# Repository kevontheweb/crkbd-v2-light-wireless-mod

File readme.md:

# corne v2 light wireless mod

- [x] change to use more generic kicad 8/9 symbols/footprints
- [x] use the DRC
- [x] add jst for battery
- [ ] pwr switch
- [ ] remove reset switch?
- [x] add the pins on the pro micro footprint for battery
- [x] aesthetic changes (font, hatched copper pour)
- [x] ~panelise~ mouse bites
- [x] use smd diodes
- [x] remove choc support (would rather have a proper choc spacing)

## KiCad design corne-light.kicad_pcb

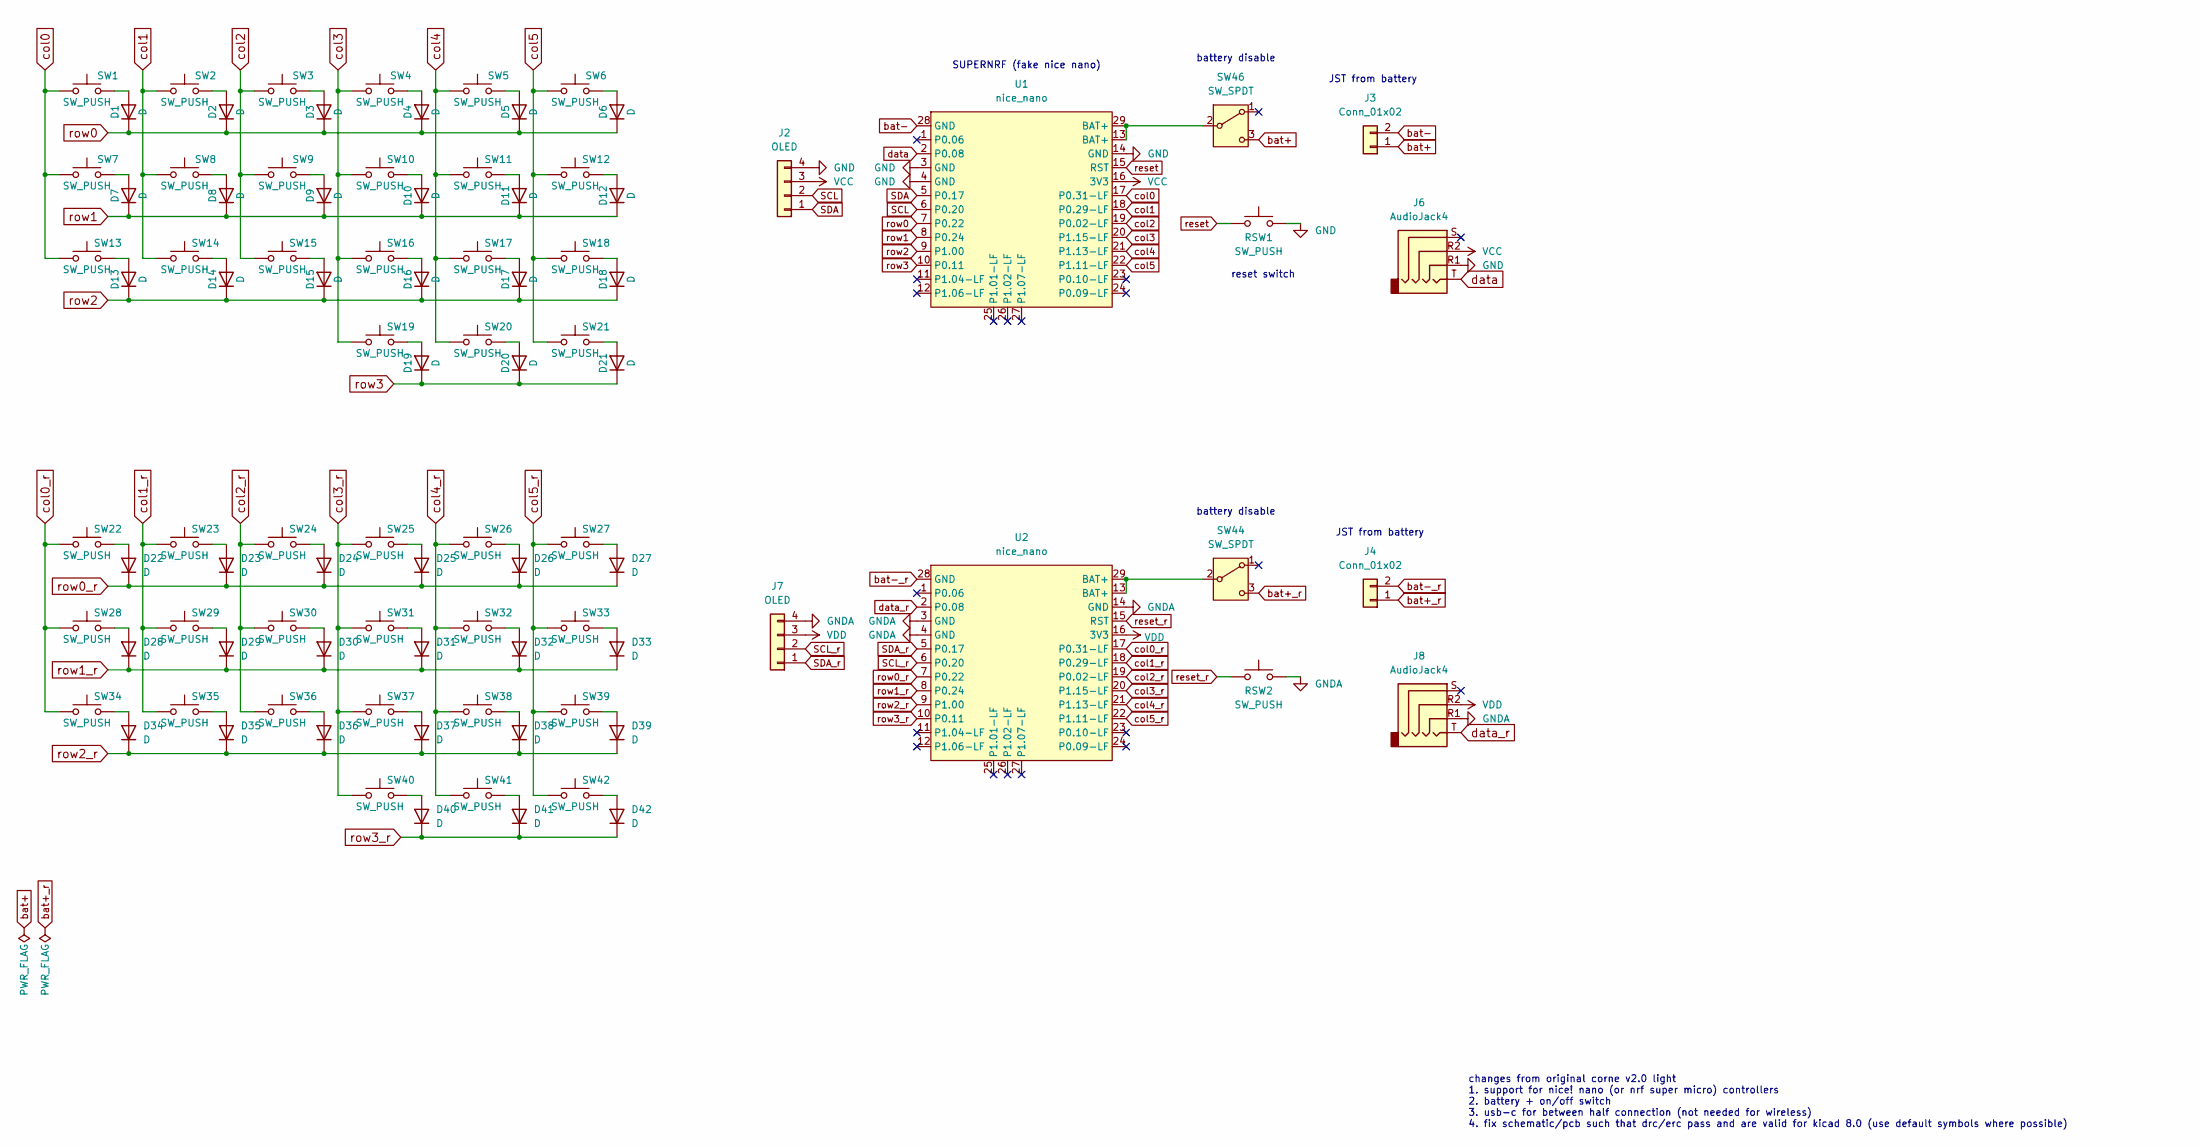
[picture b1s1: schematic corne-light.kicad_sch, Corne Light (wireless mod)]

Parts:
D1, D2, D3, D4, D5, D6, D7, D8, D9, D10, D11, D12, D13, D14, D15, D16, D17, D18, D19, D20, D21, D22, D23, D24, D25, D26, D27, D28, D29, D30, D31, D32, D33, D34, D35, D36, D37, D38, D39, D40, D41, D42: D; D_SOD-123
J2, J7: OLED
J3, J4: Conn_01x02; JST_PH_S2B-PH-K_1x02_P2.00mm_Horizontal
J6: AudioJack4; PJ320A
J8: AudioJack4; PJ320A; MPN PJ-320A; LCSC C22459514
RSW1, RSW2: SW_PUSH; SW_PUSH_1P1T_6x3.5mm_H4.3_APEM_MJTP1243
SW1, SW2, SW3, SW4, SW5, SW6, SW7, SW8, SW9, SW10, SW11, SW12, SW13, SW14, SW15, SW16, SW17, SW18, SW19, SW20, SW21, SW22, SW23, SW24, SW25, SW26, SW27, SW28, SW29, SW30, SW31, SW32, SW33, SW34, SW35, SW36, SW37, SW38, SW39, SW40, SW41, SW42: SW_PUSH; SW_Cherry_MX_PCB_1.00u
SW44, SW46: SW_SPDT; MSK-12C01-07(1P2T)
U1, U2: nice_nano; SuperMini_nRF52840_AH_Reversible

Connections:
GND: J2.4, J6.R1, RSW1.2, U1.3 (GND), U1.4 (GND), U1.14 (GND)
GNDA: J7.4, J8.R1, RSW2.2, U2.3 (GND), U2.4 (GND), U2.14 (GND)
unnamed: D1.2 (A), SW1.2
unnamed: D2.2 (A), SW2.2
unnamed: D3.2 (A), SW3.2
unnamed: D4.2 (A), SW4.2
unnamed: D5.2 (A), SW5.2
unnamed: D6.2 (A), SW6.2
unnamed: D7.2 (A), SW7.2
unnamed: D8.2 (A), SW8.2
unnamed: D9.2 (A), SW9.2
unnamed: D10.2 (A), SW10.2
unnamed: D11.2 (A), SW11.2
unnamed: D12.2 (A), SW12.2
unnamed: D13.2 (A), SW13.2
unnamed: D14.2 (A), SW14.2
unnamed: D15.2 (A), SW15.2
unnamed: D16.2 (A), SW16.2
unnamed: D17.2 (A), SW17.2
unnamed: D18.2 (A), SW18.2
unnamed: D19.2 (A), SW19.2
unnamed: D20.2 (A), SW20.2
unnamed: D21.2 (A), SW21.2
unnamed: D22.2 (A), SW22.2
unnamed: D23.2 (A), SW23.2
unnamed: D24.2 (A), SW24.2
unnamed: D25.2 (A), SW25.2
unnamed: D26.2 (A), SW26.2
unnamed: D27.2 (A), SW27.2
unnamed: D28.2 (A), SW28.2
unnamed: D29.2 (A), SW29.2
unnamed: D30.2 (A), SW30.2
unnamed: D31.2 (A), SW31.2
unnamed: D32.2 (A), SW32.2
unnamed: D33.2 (A), SW33.2
unnamed: D34.2 (A), SW34.2
unnamed: D35.2 (A), SW35.2
unnamed: D36.2 (A), SW36.2
unnamed: D37.2 (A), SW37.2
unnamed: D38.2 (A), SW38.2
unnamed: D39.2 (A), SW39.2
unnamed: D40.2 (A), SW40.2
unnamed: D41.2 (A), SW41.2
unnamed: D42.2 (A), SW42.2
unnamed: SW44.2 (B), U2.13 (BAT+), U2.29 (BAT+)
unnamed: SW46.2 (B), U1.13 (BAT+), U1.29 (BAT+)
SCL: J2.2, U1.6 (P0.20)
SCL_r: J7.2, U2.6 (P0.20)
SDA: J2.1, U1.5 (P0.17)
SDA_r: J7.1, U2.5 (P0.17)
VCC: J2.3, J6.R2, U1.16 (3V3)
VDD: J7.3, J8.R2, U2.16 (3V3)
bat+: J3.1, SW46.3 (C)
bat+_r: J4.1, SW44.3 (C)
bat-: J3.2, U1.28 (GND)
bat-_r: J4.2, U2.28 (GND)
col0: SW1.1, SW7.1, SW13.1, U1.17 (P0.31-LF)
col0_r: SW22.1, SW28.1, SW34.1, U2.17 (P0.31-LF)
col1: SW2.1, SW8.1, SW14.1, U1.18 (P0.29-LF)
col1_r: SW23.1, SW29.1, SW35.1, U2.18 (P0.29-LF)
col2: SW3.1, SW9.1, SW15.1, U1.19 (P0.02-LF)
col2_r: SW24.1, SW30.1, SW36.1, U2.19 (P0.02-LF)
col3: SW4.1, SW10.1, SW16.1, SW19.1, U1.20 (P1.15-LF)
col3_r: SW25.1, SW31.1, SW37.1, SW40.1, U2.20 (P1.15-LF)
col4: SW5.1, SW11.1, SW17.1, SW20.1, U1.21 (P1.13-LF)
col4_r: SW26.1, SW32.1, SW38.1, SW41.1, U2.21 (P1.13-LF)
col5: SW6.1, SW12.1, SW18.1, SW21.1, U1.22 (P1.11-LF)
col5_r: SW27.1, SW33.1, SW39.1, SW42.1, U2.22 (P1.11-LF)
data: J6.T, U1.2 (P0.08)
data_r: J8.T, U2.2 (P0.08)
reset: RSW1.1, U1.15 (RST)
reset_r: RSW2.1, U2.15 (RST)
row0: D1.1 (K), D2.1 (K), D3.1 (K), D4.1 (K), D5.1 (K), D6.1 (K), U1.7 (P0.22)
row0_r: D22.1 (K), D23.1 (K), D24.1 (K), D25.1 (K), D26.1 (K), D27.1 (K), U2.7 (P0.22)
row1: D7.1 (K), D8.1 (K), D9.1 (K), D10.1 (K), D11.1 (K), D12.1 (K), U1.8 (P0.24)
row1_r: D28.1 (K), D29.1 (K), D30.1 (K), D31.1 (K), D32.1 (K), D33.1 (K), U2.8 (P0.24)
row2: D13.1 (K), D14.1 (K), D15.1 (K), D16.1 (K), D17.1 (K), D18.1 (K), U1.9 (P1.00)
row2_r: D34.1 (K), D35.1 (K), D36.1 (K), D37.1 (K), D38.1 (K), D39.1 (K), U2.9 (P1.00)
row3: D19.1 (K), D20.1 (K), D21.1 (K), U1.10 (P0.11)
row3_r: D40.1 (K), D41.1 (K), D42.1 (K), U2.10 (P0.11)

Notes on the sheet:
changes from original corne v2.0 light 1. support for nice! nano (or nrf super micro) controllers 2. battery + on/off switch 3. usb-c for between half connection (not needed for wireless) 4. fix schematic/pcb such that drc/erc pass and are valid for kicad 8.0 (use default symbols where possible)
reset switch
battery disable
JST from battery
SUPERNRF (fake nice nano)

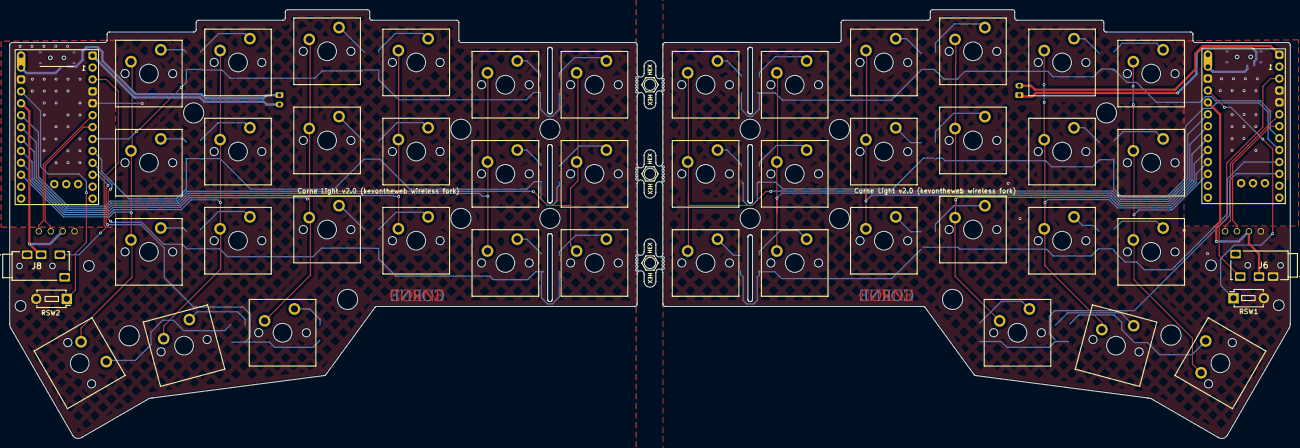
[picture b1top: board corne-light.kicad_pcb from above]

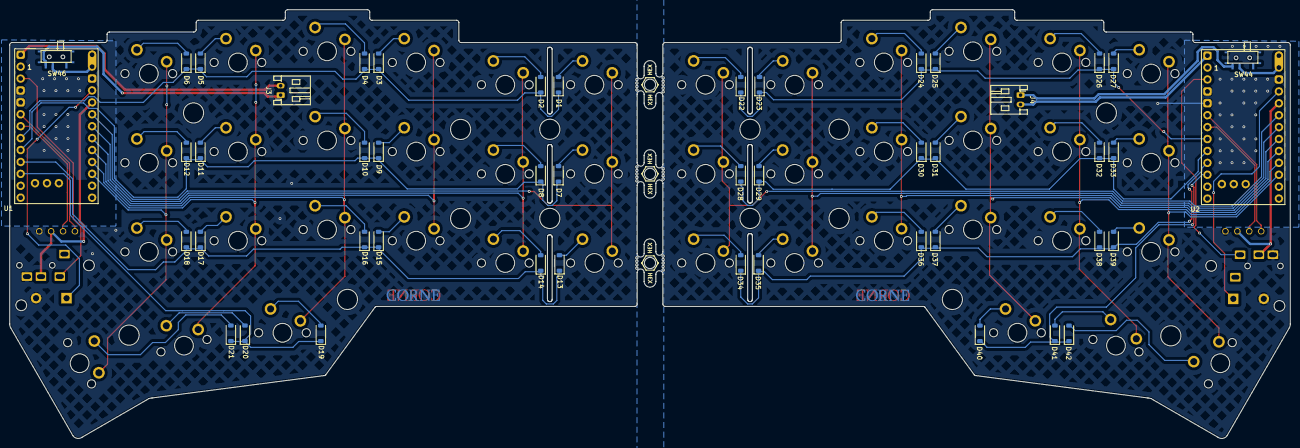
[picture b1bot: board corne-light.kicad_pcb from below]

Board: 2 copper layers, 272.9 x 91.3 mm, 117 parts (64 on the bottom side), 80 nets.

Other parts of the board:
MB5, MB5#2, MB5#3: 5.5mm; mousebites_5p5mm_easysnap
Ref**: Val**; thread_m2
Ref**#2, Ref**#8, Ref**#9: Val**; thread_m2
Ref**#3, Ref**#4, Ref**#5, Ref**#6, Ref**#7, Ref**#10, Ref**#11, Ref**#12, Ref**#13, Ref**#14, Ref**#15, Ref**#16, Ref**#17, Ref**#18: Val**; spacer_m2

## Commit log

2024-10-22 swap stupid trrs for usb-c
2024-10-22 panelised
2024-10-26 put jacks back, erc and drc. finishing touches
2024-10-26 prod
2025-02-04 update prod files and project to v9
